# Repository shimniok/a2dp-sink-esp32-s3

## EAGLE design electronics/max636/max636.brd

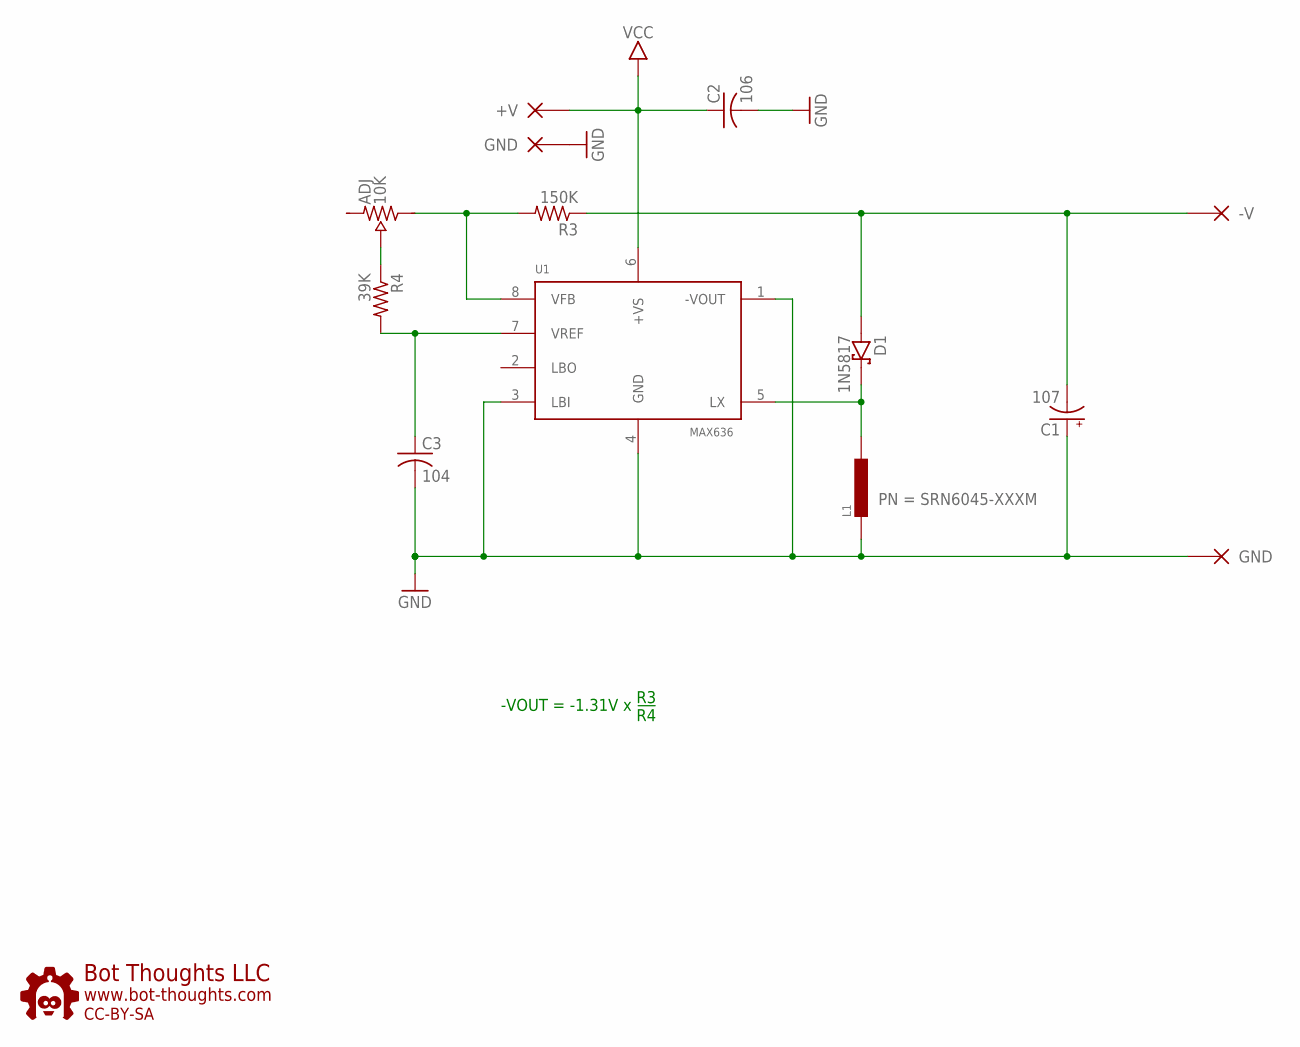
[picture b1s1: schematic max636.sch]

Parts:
ADJ: 10K; 35WR
C1: 107; SMC_B
C2: 106; 0603
C3: 104; 0603
D1: 1N5817; SOD-323
J1: +V; 1X01-S
J2: -V; 1X01-S
J3, J4: GND; 1X01-S
L1: INDUCTOR-VLS6045EX; VLS6045EX
R3: 150K; 0603
R4: 39K; 0603
U1: MAX636; SO08
U$1: BTLOGO-LOGO-SM; BTLOGOS

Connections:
GND: C1.+, C2.2 (-), C3.2 (-), J3.1, J4.1, L1.1, U1.1 (-VOUT), U1.3 (LBI), U1.4 (GND)
unnamed: D1.C, L1.2, U1.5 (LX)
unnamed: ADJ.1 (A), R3.2, U1.8 (VFB)
unnamed: C1.-, D1.A, J2.1, R3.1
unnamed: ADJ.2 (WIPER), R4.1
unnamed: C3.1 (+), R4.2, U1.7 (VREF)
VCC: C2.1 (+), J1.1, U1.6 (+VS)

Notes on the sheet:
-VOUT = -1.31V x
R3 R4

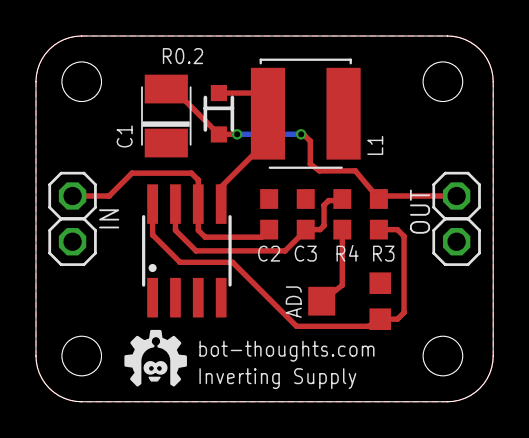
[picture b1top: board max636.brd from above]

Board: 2 copper layers, 25.4 x 20.3 mm, 14 parts (0 on the bottom side), 7 nets.

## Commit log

2024-06-13 rev 0.1
2024-06-13 revised pot
2024-06-13 added gitignore
2024-06-13 added calcs spreadsheet
2024-06-13 layout tweaks
2024-06-13 smaller mounting holes, updated gerbers
2024-06-13 changed board dimensions, revised layout
2024-06-13 updated gerbers, zip
2024-06-13 moved max636 supply board dir

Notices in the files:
parts and their libraries:
bt: CC-BY-SA
